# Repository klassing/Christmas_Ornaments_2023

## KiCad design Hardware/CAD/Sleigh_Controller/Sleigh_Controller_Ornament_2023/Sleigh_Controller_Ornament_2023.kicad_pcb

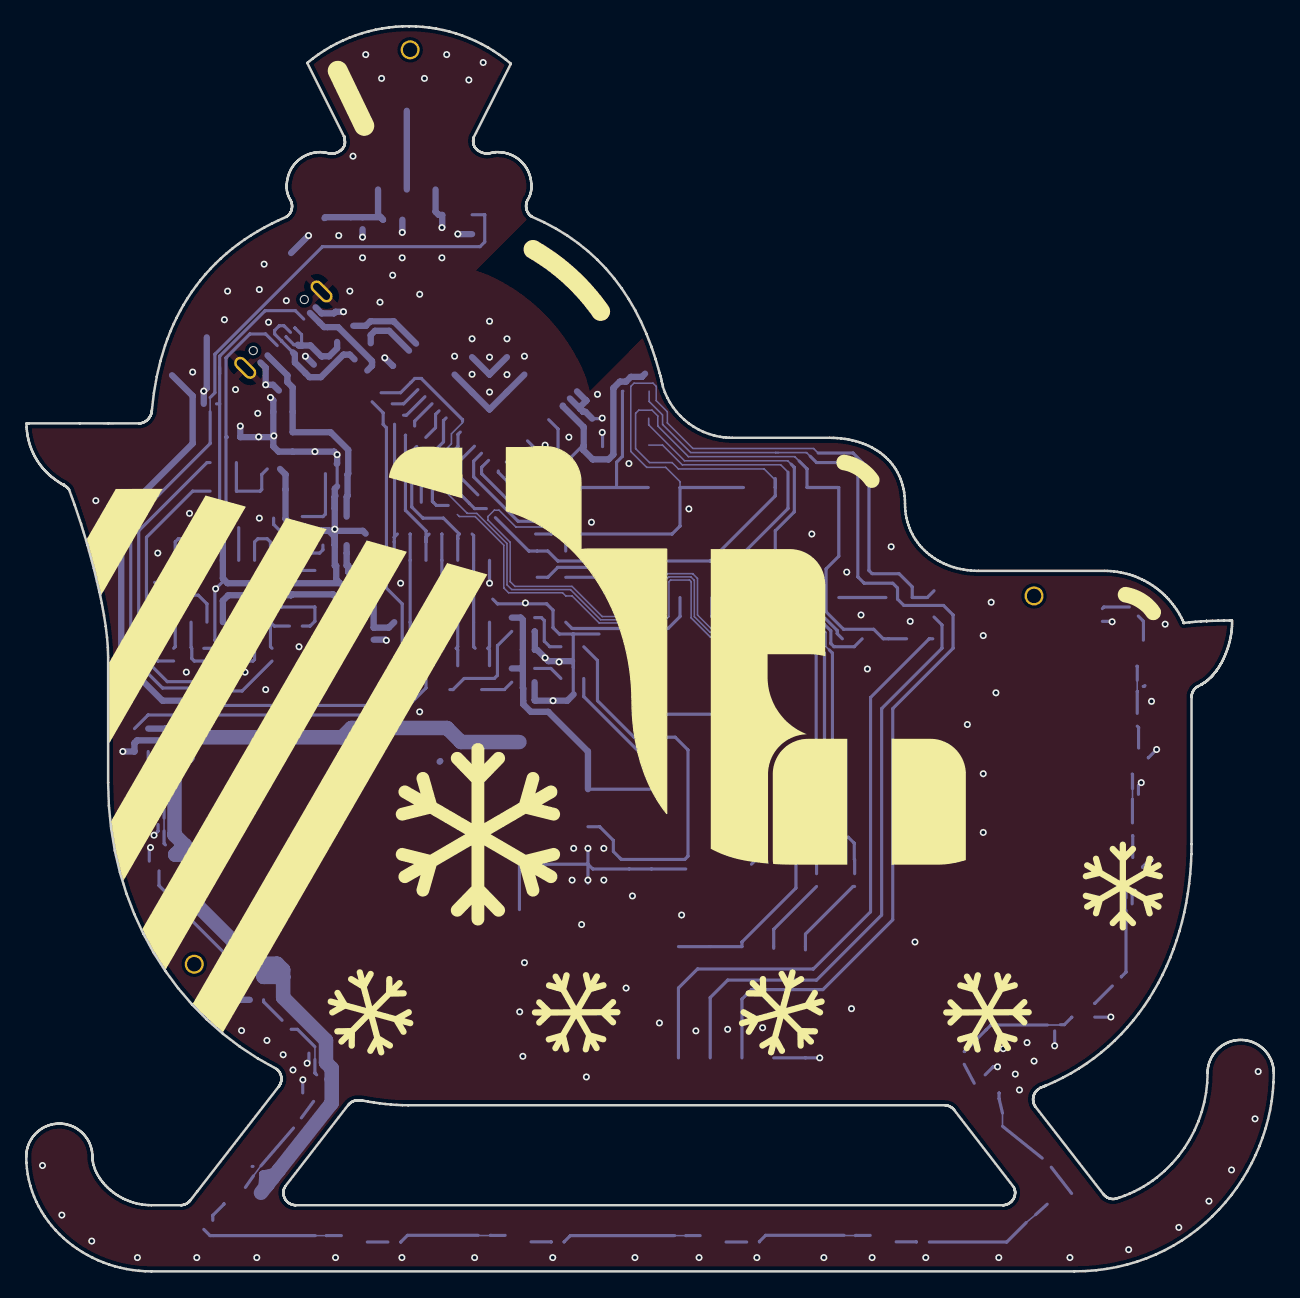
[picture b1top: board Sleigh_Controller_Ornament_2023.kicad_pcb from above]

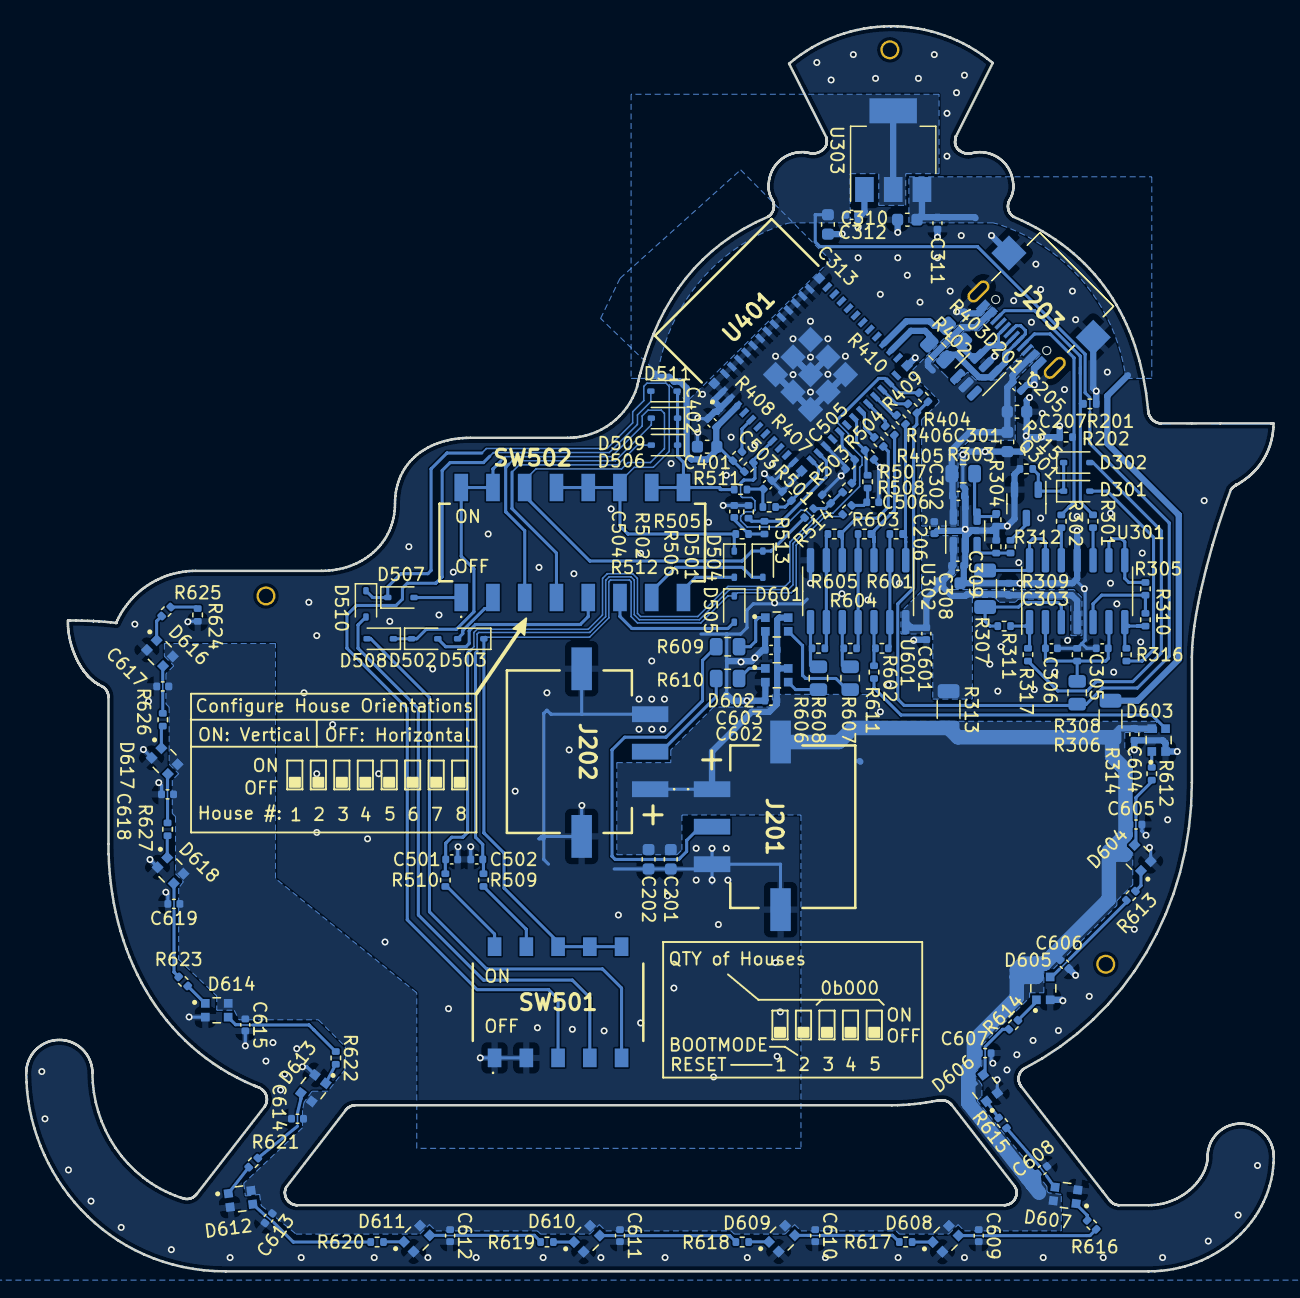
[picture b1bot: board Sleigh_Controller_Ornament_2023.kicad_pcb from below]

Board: 4 copper layers, 99.8 x 99.6 mm, 156 parts (153 on the bottom side), 105 nets.

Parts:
C201, C202, C207, C301, C309, C310, C313, C401: 10uF 10V 0603; C_0603_1608Metric
C205, C206, C302, C303, C305, C306, C308, C311, C312, C402, C501, C502, C503, C504, C505, C506, C601, C602, C603, C604, C605, C606, C607, C608, C609, C610, C611, C612, C613, C614, C615, C617, C618, C619: 0.1uF 16V 0402; C_0402_1005Metric
D201: SRV05-4; SOT-23-6
D301, D302, D501, D502, D503, D504, D505, D506, D507, D508, D509, D510, D511: 350mA 28V; D_SOD-323
D601, D602, D603, D604, D605, D606, D607, D608, D609, D610, D611, D612, D613, D614, D616, D617, D618: WS2812B-2020; LED_WS2812B-2020
H101, H102, H103: JLC Tooling Hole; JLC_Tooling
J201, J202: 3mm Pitch 5A - 3p; 20290303
J203: GT-USB-7047C
Q301: 20V 28mOhm; SOT-23-3
R201, R202, R301, R302, R304, R308: 5.1k 1% 0402; R_0402_1005Metric
R303: 0ohm 0805; R_0805_2012Metric
R305: 4.7k 1% 0402; R_0402_1005Metric
R306: 20k 1% 0805; R_0805_2012Metric
R307: 4.7k 1% 1206; R_1206_3216Metric
R309, R315, R407, R408, R409, R410, R624: 10k 1% 0402; R_0402_1005Metric
R310, R311: 150k 1% 0402; R_0402_1005Metric
R312: 8.2k 1% 0402; R_0402_1005Metric
R313, R314: 0ohm 1206; R_1206_3216Metric
R316, R317, R404, R405, R406, R611, R612, R613, R614, R615, R616, R617, R618, R619, R620, R621, R622, R623, R625, R626, R627: 33 1% 0402; R_0402_1005Metric
R402, R403, R607, R608, R609, R610: 33 1% 0805; R_0805_2012Metric
R501, R502, R503, R504: 510k 1% 0402; R_0402_1005Metric
R505, R506, R507, R508, R509, R510, R511, R512, R513, R514: 1k 1% 0402; R_0402_1005Metric
R601, R602, R603, R604, R605, R606: 0 1% 0402; R_0402_1005Metric
SW501: SW_DIP_x05_alt; EM-05KP
SW502: SW_DIP_x08; SMXS-08K-TP
U301: LMV324; SO-14_3.9x8.65mm_P1.27mm
U302: MT9700; SOT-23-5
U303: AMS1117-3.3; SOT-223-3_TabPin2
U401: ESP32-C3-MINI-1-N4
U601: 74HC14D,653; SO-14_3.9x8.65mm_P1.27mm

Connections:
/Charlieplexing/CMUX_0_3V3: R501.1, R505.2, U401.12 (IO0/ADC1_CH0/XTAL_32K_P)
/Charlieplexing/CMUX_0_RC_3V3: C503.1, R505.1, R511.2
/Charlieplexing/CMUX_0_SW_3V3: D506.1 (A1), D509.1 (A1), D511.1 (A1), R511.1, SW502.9, SW502.10
/Charlieplexing/CMUX_1_3V3: R502.1, R506.2, U401.13 (IO1/ADC1_CH1/XTAL_32K_N)
/Charlieplexing/CMUX_1_RC_3V3: C504.1, R506.1, R512.2
/Charlieplexing/CMUX_1_SW_3V3: D501.1 (A1), D507.1 (A1), D510.1 (A1), R512.1, SW502.11, SW502.12, SW502.13
/Charlieplexing/CMUX_2_3V3: R503.1, R507.2, U401.16 (IO10/FSPICS0)
/Charlieplexing/CMUX_2_RC_3V3: C505.1, R507.1, R513.2
/Charlieplexing/CMUX_2_SW_3V3: D502.1 (A1), D504.1 (A1), D508.1 (A1), R513.1, SW502.14, SW502.15, SW502.16
/Charlieplexing/CMUX_3_3V3: R504.1, R508.2, U401.18 (IO4/ADC1_CH4/FSPIHD/MTMS)
/Charlieplexing/CMUX_3_RC_3V3: C506.1, R508.1, R514.2
/Charlieplexing/CMUX_3_SW_3V3: D503.1 (A1), D505.1 (A1), R514.1, SW501.6, SW501.7, SW501.8
/Charlieplexing/MCU_BOOTMODE_3V3: C502.1, R410.2, R509.2, U401.23 (IO9)
/Charlieplexing/MCU_EN_3V3: C501.1, R407.2, R510.2, U401.8 (EN)
/Connectors/LED_DWN_OUT_5V0: J202.2, R610.1
/Connectors/LED_UP_OUT_5V0: J201.2, R609.1
/Connectors/USB_CC1: J203.A5 (CC1), R202.1, R302.2
/Connectors/USB_CC2: J203.B5 (CC2), R201.1, R301.1
/Connectors/USB_DM: D201.1 (I/O1), J203.A7 (D-), J203.B7 (D-), R402.2
/Connectors/USB_DP: D201.3 (I/O2), J203.A6 (D+), J203.B6 (D+), R403.2
/LEDs/LED_DWN_EXT_3V3: R405.2, R605.2, U601.5
/LEDs/LED_INT_3V3: R404.2, R601.2, U601.1
/LEDs/LED_UP_EXT_3V3: R406.2, R603.2, U601.3
/MCU/USB_DM_ESP: R402.1, U401.26 (USB_DM/IO18)
/MCU/USB_DP_ESP: R403.1, U401.27 (USB_DP/IO19)
/Power/LDO_IN_5V0: C310.1, C311.1, R314.1, U303.3 (VI)
GND: C201.2, C202.2, C205.2, C206.2, C207.2, C301.2, C302.2, C303.2, C305.1, C306.1, C308.2, C309.2, C310.2, C311.2, C312.2, C313.2, C401.2, C402.2, C501.2, C502.2, C503.2, C504.2, C505.2, C506.2, C601.2, C602.2, C603.2, C604.2, C605.2, C606.2, C607.2, C608.2, C609.2, C610.2, C611.2, C612.2, C613.2, C614.2, C615.2, C617.2, C618.2, C619.2, D201.2 (GND), D601.2 (VSS), D602.2 (VSS), D603.2 (VSS), D604.2 (VSS), D605.2 (VSS), D606.2 (VSS), D607.2 (VSS), D608.2 (VSS), D609.2 (VSS), D610.2 (VSS), D611.2 (VSS), D612.2 (VSS), D613.2 (VSS), D614.2 (VSS), D616.2 (VSS), D617.2 (VSS), D618.2 (VSS), J201.3, J201.MP1, J202.3, J202.MP1, J202.MP2, J203.A1 (GND), J203.A12 (GND), J203.B1 (GND), J203.B12 (GND), J203.S1 (SHIELD), Q301.2 (S), R201.2, R202.2, R304.1, R308.1, R309.1, R315.1, R501.2, R502.2, R503.2, R504.2, R624.2, SW501.1, SW501.2, U301.11 (V-), U302.2 (GND), U303.1 (GND), U401.1 (GND), U401.2 (GND), U401.11 (GND), U401.14 (GND), U401.36 (GND), U401.37 (GND), U401.38 (GND), U401.39 (GND), U401.40 (GND), U401.41 (GND), U401.42 (GND), U401.43 (GND), U401.44 (GND), U401.45 (GND), U401.46 (GND), U401.47 (GND), U401.48 (GND), U401.49 (EPAD), U401.50 (EPAD), U401.51 (EPAD), U401.52 (EPAD), U401.53 (EPAD), U401.54 (EPAD), U401.55 (EPAD), U401.56 (EPAD), U401.57 (EPAD), U401.58 (MPAD), U401.59 (MPAD), U401.60 (MPAD), U401.61 (MPAD), U601.7 (GND)
unnamed: D301.1 (A1), D302.1 (A1), Q301.1 (G), R315.2
unnamed: D301.2 (A2), R316.1
unnamed: D302.2 (A2), R317.1
unnamed: D501.2 (A2), SW502.8
unnamed: D502.2 (A2), SW502.5
unnamed: D503.2 (A2), SW502.2
unnamed: D504.2 (A2), SW502.7
unnamed: D505.2 (A2), SW502.6
unnamed: D506.2 (A2), SW502.4
unnamed: D507.2 (A2), SW502.1
unnamed: D508.2 (A2), SW501.5
unnamed: D509.2 (A2), SW502.3
unnamed: D510.2 (A2), SW501.4
unnamed: D511.2 (A2), SW501.3
unnamed: D601.3 (DIN), R607.1
unnamed: D601.1 (DOUT), R609.2
unnamed: D602.3 (DIN), R608.1
unnamed: D602.1 (DOUT), R610.2
unnamed: D603.3 (DIN), R611.1
unnamed: D603.1 (DOUT), R612.2
unnamed: D604.3 (DIN), R612.1
unnamed: D604.1 (DOUT), R613.2
unnamed: D605.3 (DIN), R613.1
unnamed: D605.1 (DOUT), R614.2
unnamed: D606.3 (DIN), R614.1
unnamed: D606.1 (DOUT), R615.2
unnamed: D607.3 (DIN), R615.1
unnamed: D607.1 (DOUT), R616.2
unnamed: D608.3 (DIN), R616.1
unnamed: D608.1 (DOUT), R617.2
unnamed: D609.3 (DIN), R617.1
unnamed: D609.1 (DOUT), R618.2
unnamed: D610.3 (DIN), R618.1
unnamed: D610.1 (DOUT), R619.2
unnamed: D611.3 (DIN), R619.1
unnamed: D611.1 (DOUT), R620.2
unnamed: D612.3 (DIN), R620.1
unnamed: D612.1 (DOUT), R621.2
unnamed: D613.3 (DIN), R621.1
unnamed: D613.1 (DOUT), R622.2
unnamed: D614.3 (DIN), R622.1
unnamed: D614.1 (DOUT), R623.2
unnamed: D616.3 (DIN), R626.1
unnamed: D616.1 (DOUT), R625.2
unnamed: D617.3 (DIN), R627.1
unnamed: D617.1 (DOUT), R626.2
unnamed: D618.3 (DIN), R623.1
unnamed: D618.1 (DOUT), R627.2
unnamed: Q301.3 (D), R312.1
unnamed: R310.1, R316.2, U301.7
unnamed: R311.1, R317.2, U301.1
unnamed: R509.1, SW501.9
unnamed: R510.1, SW501.10
unnamed: R601.1, R602.2, U601.2, U601.13
unnamed: R602.1, R611.2, U601.12
unnamed: R603.1, R604.2, U601.4, U601.11
unnamed: R604.1, R607.2, U601.10
unnamed: R605.1, R606.2, U601.6, U601.9
unnamed: R606.1, R608.2, U601.8
unnamed: R624.1, R625.1
unnamed: R307.1, R311.2, U301.3 (+)
unnamed: C305.2, C306.2, R306.1, R308.2, U301.2 (-), U301.6 (-)
unnamed: R305.1, R310.2, U301.5 (+)
unnamed: R301.2, U301.10 (+)
unnamed: R305.2, U301.8, U301.9 (-)
unnamed: R302.1, U301.12 (+)
unnamed: R307.2, U301.13 (-), U301.14
unnamed: R303.1, R304.2, U302.4 (EN)
unnamed: R309.2, R312.2, U302.3 (SET)
unnamed: R408.2, U401.5 (IO2/ADC1_CH2/FSPIQ)
unnamed: R405.1, U401.19 (IO5/ADC2_CH0_FSPIWP/MTDI)
unnamed: R406.1, U401.20 (IO6/FSPICLK/MTCK)
unnamed: R404.1, U401.21 (IO7/FSPID/MTDO)
unnamed: R409.2, U401.22 (IO8)
VBUS_5V0: C205.1, C206.1, C207.1, C301.1, C302.1, D201.5 (REF), J203.A4 (VBUS), J203.A9 (VBUS), J203.B4 (VBUS), J203.B9 (VBUS), R303.2, U302.5 (VIN)
VDD_3V3: C312.1, C313.1, C401.1, C402.1, R306.2, R407.1, R408.1, R409.1, R410.1, U303.2 (VO), U401.3 (3V3)
VLED_5V0: C201.1, C202.1, C602.1, C603.1, C604.1, C605.1, C606.1, C607.1, C608.1, C609.1, C610.1, C611.1, C612.1, C613.1, C614.1, C615.1, C617.1, C618.1, C619.1, D601.4 (VDD), D602.4 (VDD), D603.4 (VDD), D604.4 (VDD), D605.4 (VDD), D606.4 (VDD), D607.4 (VDD), D608.4 (VDD), D609.4 (VDD), D610.4 (VDD), D611.4 (VDD), D612.4 (VDD), D613.4 (VDD), D614.4 (VDD), D616.4 (VDD), D617.4 (VDD), D618.4 (VDD), J201.1, J201.MP2, J202.1, R313.2, R314.2
VLED_JUMP_5V0: C303.1, C308.1, C309.1, C601.1, R313.1, U301.4 (V+), U302.1 (VOUT), U601.14 (VCC)

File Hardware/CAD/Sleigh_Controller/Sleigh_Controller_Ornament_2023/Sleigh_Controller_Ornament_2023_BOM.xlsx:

Source: | C:\Users\Ryan\Projects\Christmas_Ornaments_2023\Hardware\CAD\Sleigh_Controller\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
Date: | 45252.595671296294
Tool: | Eeschema 7.0.9
Generator: | C:\Program Files\KiCad\7.0\bin\scripting\plugins/bom_csv_grouped_by_value.py
Component Count: | 165
Collated Components:
Item | Qty | Reference(s) | Value | LibPart | Footprint | Datasheet | DNP | Description | Height | JLC_Cost | JLC_MPN | JLC_Manufacturer | JLC_PN | JLC_Type | Manufacturer_Name | Manufacturer_Part_Number | Mouser Part Number | Mouser Price/Stock
1 | 39 | C201, C202, C205, C206, C302, C303, C304, C305, C306, C307, C308, C311, C312, C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 | 0.1uF 16V 0402 | Device:C_Small | Capacitor_SMD:C_0402_1005Metric | ~ |  |  |  | 8.9999999999999998E-4 | CL05B104KO5NNNC | Samsung Electro-Mechanics | C1525 | Basic
2 | 9 | C203, C204, C207, C208, C301, C309, C310, C313, C401 | 10uF 10V 0603 | Device:C_Small | Capacitor_SMD:C_0603_1608Metric | ~ |  |  |  | 5.0000000000000001E-3 | CL10A106KP8NNNC | Samsung Electro-Mechanics | C19702 | Basic
3 | 1 | D201 | SRV05-4 | RK_Power_Protection:SRV05-4 | Package_TO_SOT_SMD:SOT-23-6 | http://www.protekdevices.com/xyz/documents/datasheets/srv05_4.pdf |  |  |  | 4.7600000000000003E-2 | SRV05-4 | hongjiacheng | C7420376 | Basic
4 | 13 | D301, D302, D501, D502, D503, D504, D505, D506, D507, D508, D509, D510, D511 | 350mA 28V | RK_Diodes:350mA 28V SOD-323 | Diode_SMD:D_SOD-323 | https://datasheet.lcsc.com/lcsc/2308281515_hongjiacheng-SD10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 |  |  |  | 6.4999999999999997E-3 | SD103AWS | hongjiacheng | C7420360 | Basic
5 | 18 | D601, D602, D603, D604, D605, D606, D607, D608, D609, D610, D611, D612, D613, D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 | WS2812B-2020 | RK_LED:WS2812B-2020 | RK_LED_SMD:LED_WS2812B-2020 | https://www.mouser.com/pdfDocs/WS2812B-2020_V10_EN_181106150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 |  |  |  | 9.2600000000000002E-2 | WS2812B-2020 | Worldsemi | C965555 | Extended
6 | 3 | H101, H102, H103 | JLC Tooling Hole | RK_Holes:JLC Tooling Hole | RK_Holes:JLC_Tooling | ~
7 | 2 | J201, J202 | 3mm Pitch 5A - 3p | RK_Connector_Terminals:3mm Pitch 5A - 3p | RK_Connector_Terminals:20290303 | https://www.te.com/commerce/DocumentDelivery/DDEController?A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 |  | 3P MICRO MNL HDR ASY SR SIDE L | 4.37 | 0.38 |  | XKB Connectivity | C405941 | Extended | TE Connectivity | 2029030-3 | 571-2029030-3 | https://www.mouser.co.uk/ProductDetail/TE-Connectivity-AMP/2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
8 | 1 | J203 | GT-USB-7047C | RK_Connector_USB:GT-USB-7047C | RK_Connector_USB:GT-USB-7047C | https://datasheet.lcsc.com/lcsc/2303032030_G-Switch-GT-USB-7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 |  |  |  | 0.19989999999999999 | GT-USB-7047C | G-Switch | C963218 | Extended
9 | 1 | Q301 | 20V 28mOhm | RK_Transistor_FET:20V 28mOhm N-CH SI2302 | Package_TO_SOT_SMD:SOT-23-3 | https://datasheet.lcsc.com/lcsc/2308231035_MDD-Microdiode-El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 |  |  |  |  | MDD2302 | MDD | C427390 | Basic
10 | 6 | R201, R202, R301, R302, R304, R308 | 5.1k 1% 0402 | Device:R_Small_US | Resistor_SMD:R_0402_1005Metric | ~ |  |  |  | 5.0000000000000001E-4 | 0402WGF5101TCE | UNI-ROYAL(Uniroyal Elec) | C25905 | Basic
11 | 4 | R303, R313, R314, R401 | 0ohm 0805 | Device:R_Small_US | Resistor_SMD:R_0805_2012Metric | ~ |  |  |  | 1.6000000000000001E-3 | 0805W8F0000T5E | UNI-ROYAL(Uniroyal Elec) | C17477 | Basic
12 | 2 | R305, R307 | 4.7k 1% 1206 | Device:R_Small_US | Resistor_SMD:R_1206_3216Metric | ~ |  |  |  | 2.7000000000000001E-3 | 1206W4F4701T5E | UNI-ROYAL(Uniroyal Elec) | C17936 | Basic
13 | 1 | R306 | 20k 1% 0402 | Device:R_Small_US | Resistor_SMD:R_0402_1005Metric | ~ |  |  |  | 4.0000000000000002E-4 | 0402WGF2002TCE | UNI-ROYAL(Uniroyal Elec) | C25765 | Basic
14 | 7 | R309, R315, R407, R408, R409, R410, R628 | 10k 1% 0402 | Device:R_Small_US | Resistor_SMD:R_0402_1005Metric | ~ |  |  |  | 4.0000000000000002E-4 | 0402WGF1002TCE | UNI-ROYAL(Uniroyal Elec) | C25744 | Basic
15 | 2 | R310, R311 | 150k 1% 0402 | Device:R_Small_US | Resistor_SMD:R_0402_1005Metric | ~ |  |  |  | 4.0000000000000002E-4 | 0402WGF1503TCE | UNI-ROYAL(Uniroyal Elec) | C25755 | Basic
16 | 1 | R312 | 8.2k 1% 0402 | Device:R_Small_US | Resistor_SMD:R_0402_1005Metric | ~ |  |  |  | 5.0000000000000001E-4 | 0402WGF8201TCE | UNI-ROYAL(Uniroyal Elec) | C25924 | Basic
17 | 28 | R316, R317, R402, R403, R404, R405, R406, R607, R608, R609, R610, R611, R612, R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 | 33 1% 0402 | Device:R_Small_US | Resistor_SMD:R_0402_1005Metric | ~ |  |  |  | 4.0000000000000002E-4 | 0402WGF330JTCE | UNI-ROYAL(Uniroyal Elec) | C25105 | Basic
18 | 4 | R501, R502, R503, R504 | 510k 1% 0402 | Device:R_Small_US | Resistor_SMD:R_0402_1005Metric | ~ |  |  |  | 4.0000000000000002E-4 | 0402WGF5103TCE | UNI-ROYAL(Uniroyal Elec) | C11616 | Basic
19 | 10 | R505, R506, R507, R508, R509, R510, R511, R512, R513, R514 | 1k 1% 0402 | Device:R_Small_US | Resistor_SMD:R_0402_1005Metric | ~ |  |  |  | 5.0000000000000001E-4 | 0402WGF1001TCE | UNI-ROYAL(Uniroyal Elec) | C11702 | Basic
20 | 6 | R601, R602, R603, R604, R605, R606 | 0 1% 0402 | Device:R_Small_US | Resistor_SMD:R_0402_1005Metric | ~ | DNP |  |  | 5.0000000000000001E-4 | 0402WGF0000TCE | UNI-ROYAL(Uniroyal Elec) | C17168 | Basic
21 | 1 | SW501 | SW_DIP_x05_alt | RK_Switches:SW_DIP_x05_alt | RK_Switches:EM-05KP | https://datasheet.lcsc.com/lcsc/2108131530_Korean-Hroparts-E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 |  |  |  | 0.51910000000000001 | EM-05KP | Korean Hroparts Elec | C129081 | Extended
22 | 1 | SW502 | SW_DIP_x08 | RK_Switches:SW_DIP_x08_alt | RK_Switches:SMXS-08K-TP | https://datasheet.lcsc.com/lcsc/2303301800_SM-Switch-SMXS-08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 |  |  |  | 0.61960000000000004 | SMXS-08K-TP | SM Switch | C5439767 | Extended
23 | 1 | U301 | LMV324 | RK_Amplifier_Operational:LMV324 | Package_SO:SO-14_3.9x8.65mm_P1.27mm | https://datasheet.lcsc.com/lcsc/1809051220_STMicroelectronic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 |  |  |  | 0.16300000000000001 | LM324DT | STMicroelectronics | C71035 | Basic
24 | 1 | U302 | MT9700 | RK_Power_Management:MT9700 | Package_TO_SOT_SMD:SOT-23-5 | https://datasheet.lcsc.com/lcsc/1809291208_XI-AN-Aerosemi-Te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 |  |  |  | 4.7600000000000003E-2 | MT9700 | XI'AN Aerosemi Tech | C89855 | Extended
25 | 1 | U303 | AMS1117-3.3 | RK_Regulator_Linear:AMS1117-3.3 | Package_TO_SOT_SMD:SOT-223-3_TabPin2 | http://www.advanced-monolithic.com/pdf/ds1117.pdf |  |  |  | 0.13120000000000001 |  | Advanced Monolithic Systems | C6186 | Basic
26 | 1 | U401 | ESP32-C3-MINI-1-N4 | RK_MCU_Espressif:ESP32-C3-MINI-1-N4 | RK_MCU_Modules:ESP32-C3-MINI-1-N4 | http://espressif.com/sites/default/files/documentation/0a-ht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 |  |  |  | 2.3677000000000001 | ESP32-C3-MINI-1-N4 | Espressif Systems | C2838502 | Extended
27 | 1 | U601 | 74HC14D,653 | RK_Logic_LevelTranslator:74HC14 | Package_SO:SO-14_3.9x8.65mm_P1.27mm | https://datasheet.lcsc.com/lcsc/1811141851_Nexperia-74HC14D-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 |  |  |  | 0.10349999999999999 | 74HC14D,653 | Nexperia | C5605 | Basic
 |  |  | QTY | 10 | Cost/pcb | Total/unit | Extended | BOM/unit | 8.9307000000000016
 |  |  | PCB 2L | 39.130000000000003 | 3.9130000000000003 | 12.843700000000002 | 128.43700000000001
 |  |  | PCB 2L plugged | 90.99 | 9.0990000000000002 | 18.029700000000002 | 180.29700000000003
 |  |  | PCB 4L | 67.959999999999994 | 6.7959999999999994 | 15.726700000000001 | 157.267
 |  |  | PCB 4L plugged | 85.25 | 8.5250000000000004 | 17.4557 | 174.55700000000002
 |  |  | QTY | 15 | Cost/pcb | Total/unit | Extended | BOM/unit | 8.2307000000000006
 |  |  | PCB 2L | 39.130000000000003 | 3.9130000000000003 | 12.843700000000002 | 128.43700000000001
 |  |  | PCB 2L plugged | 90.99 | 9.0990000000000002 | 18.029700000000002 | 180.29700000000003
 |  |  | PCB 4L | 67.959999999999994 | 6.7959999999999994 | 15.726700000000001 | 157.267
 |  |  | PCB 4L plugged | 113.13 | 11.312999999999999 | 20.2437 | 202.43700000000001

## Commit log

2023-11-18 Stana Sleigh: PCB Outline Finished
    Initial board outline for the santa sleigh controller is completed.
2023-12-10 PCB Progress
2023-12-10 pcb progress continued
